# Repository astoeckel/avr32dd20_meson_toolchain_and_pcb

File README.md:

# AVR32DD20 Meson Toolchain and Breadboard Adapter PCB

**[Meson](https://mesonbuild.com/)-based toolchain for the [Microchip AVR32DD20 µC](https://www.microchip.com/en-us/product/AVR32DD20
) along with a simple breadboard adapter PCB.**

> **Note**  
> While I hope that this repository may turn out useful, please be aware that it was mainly created as a reference for myself.

> **Warning**  
> I'm not an electrical engineer; please use the PCB design with utmost caution.

At the time of creating this repository, information on how to use the newer AVR µCs (DA, DB, DD, series) with fully open-source toolchains was rather spotty.
This repository has hence been created to provide a simple example that demonstrates how to compile code for these new µCs (specifically, the AVR32DD20) with the meson build system.
<div align="center">

</div>

## Meson Toolchain

### Compile the test program

To compile the test program (see  [`src/main.c`](src/main.c)), follow the following steps.
1. **Install `avrdude` and the `avr-gcc` toolchain, as well as `meson` build and `ninja`.**  
   On Fedora Linux, simply run
   ```sh
   sudo dnf install avrdude avr-gcc avr-gcc-c++ avr-binutils ninja meson
   ```
1. **Clone this repository**
   ```sh
    git clone https://github.com/astoeckel/avr32dd20_meson_toolchain_and_pcb
    cd avr32dd20_meson_toolchain_and_pcb
   ```
1. **Edit the `path` constant in `avr-unknown-gcc.txt`**  
   This constant should point at your copy of the Git repository. Right now, `meson` does not support relative paths in the toolchain definition, so the absolute path has to be inserted by hand.
3. **Create a build directory and compile**  
   ```sh
   mkdir build; cd build
   meson setup --cross-file=../avr-unknown-gcc.txt ..
   ninja
   ```

### Flash the test program

To flash the test program using `avrdude` and a `jtag2udpi`-compatible programmer (I'm using a [Diamex EXA-PROG](https://www.diamex.de/dxshop/EXA-PROG-AVR-ISP-und-UPDI-STM32-NXP-ESP)), simply run
```sh
ninja flash
```
Edit [`meson.build`](meson.build) to change the programmer parameters.

## PCB

The PCB is a simple adapter for putting AVR32DD20 in the SOIC20 onto a breadboard.
All KiCAD project files are located in the [board](board/kicad) folder; you can find the final Gerber files for production with [JLCPCB](https://jlcpcb.com/) in the [gerber](board/gerber) folder.

### Features

* **UPDI programming header**  
  The PCB includes a standard 6-pin UPDI programming header. Note that no extra resistors or diodes are included; this board assumes that you have a proper UPDI programmer that includes all required circuitry.
* **Bypass capacitors**  
  There is some space on the PCB to for 10n and 100n bypass capacitors attached to the VCC and VIO lines.
* **Quarz crystal**  
  There is some space for a quartz-crystal on the back side, along with the corresponding capacitors.

# License information

### Third-party sources

This repository contains code from various thrid-parties:

* `avrdude.conf`  
  This file has been adapted from the `jtag2updi` project (see https://github.com/ElTangas/jtag2updi); the file was extended to include the `avr32dd20` part.
* `part_definition`  
  These files have been copied from the Microchip AVR-Dx Series Device Support pack. See https://packs.download.microchip.com/ for more information.
* `avr-unknown-gcc.txt`  
  This file has been adapted from Jussi Pakkanen's Meson Arduino Project: https://github.com/jpakkane/mesonarduino

Apart from these directories, and unless noted differently, the files in this repository are licensed as follows:

### Hardware schematics

    Copyright Andreas Stöckel 2022.
    
    This documentation describes Open Hardware and is licensed under the
    CERN OHL v. 1.2. You may redistribute and modify this documentation under
    the terms of the CERN OHL v.1.2. (http://ohwr.org/cernohl). This
    documentation is distributed WITHOUT ANY EXPRESS OR IMPLIED WARRANTY,
    INCLUDING OF MERCHANTABILITY, SATISFACTORY QUALITY AND FITNESS FOR A
    PARTICULAR PURPOSE. Please see the CERN OHL v.1.2 for applicable conditions.

### Software (AVR firmware and host programs)

    Copyright (c) 2022 Andreas Stöckel

    Permission is hereby granted, free of charge, to any person obtaining a copy
    of this software and associated documentation files (the "Software"), to deal
    in the Software without restriction, including without limitation the rights
    to use, copy, modify, merge, publish, distribute, sublicense, and/or sell
    copies of the Software, and to permit persons to whom the Software is
    furnished to do so, subject to the following conditions:

    The above copyright notice and this permission notice shall be included in all
    copies or substantial portions of the Software.

    THE SOFTWARE IS PROVIDED "AS IS", WITHOUT WARRANTY OF ANY KIND, EXPRESS OR
    IMPLIED, INCLUDING BUT NOT LIMITED TO THE WARRANTIES OF MERCHANTABILITY,
    FITNESS FOR A PARTICULAR PURPOSE AND NONINFRINGEMENT. IN NO EVENT SHALL THE
    AUTHORS OR COPYRIGHT HOLDERS BE LIABLE FOR ANY CLAIM, DAMAGES OR OTHER
    LIABILITY, WHETHER IN AN ACTION OF CONTRACT, TORT OR OTHERWISE, ARISING FROM,
    OUT OF OR IN CONNECTION WITH THE SOFTWARE OR THE USE OR OTHER DEALINGS IN THE
    SOFTWARE.

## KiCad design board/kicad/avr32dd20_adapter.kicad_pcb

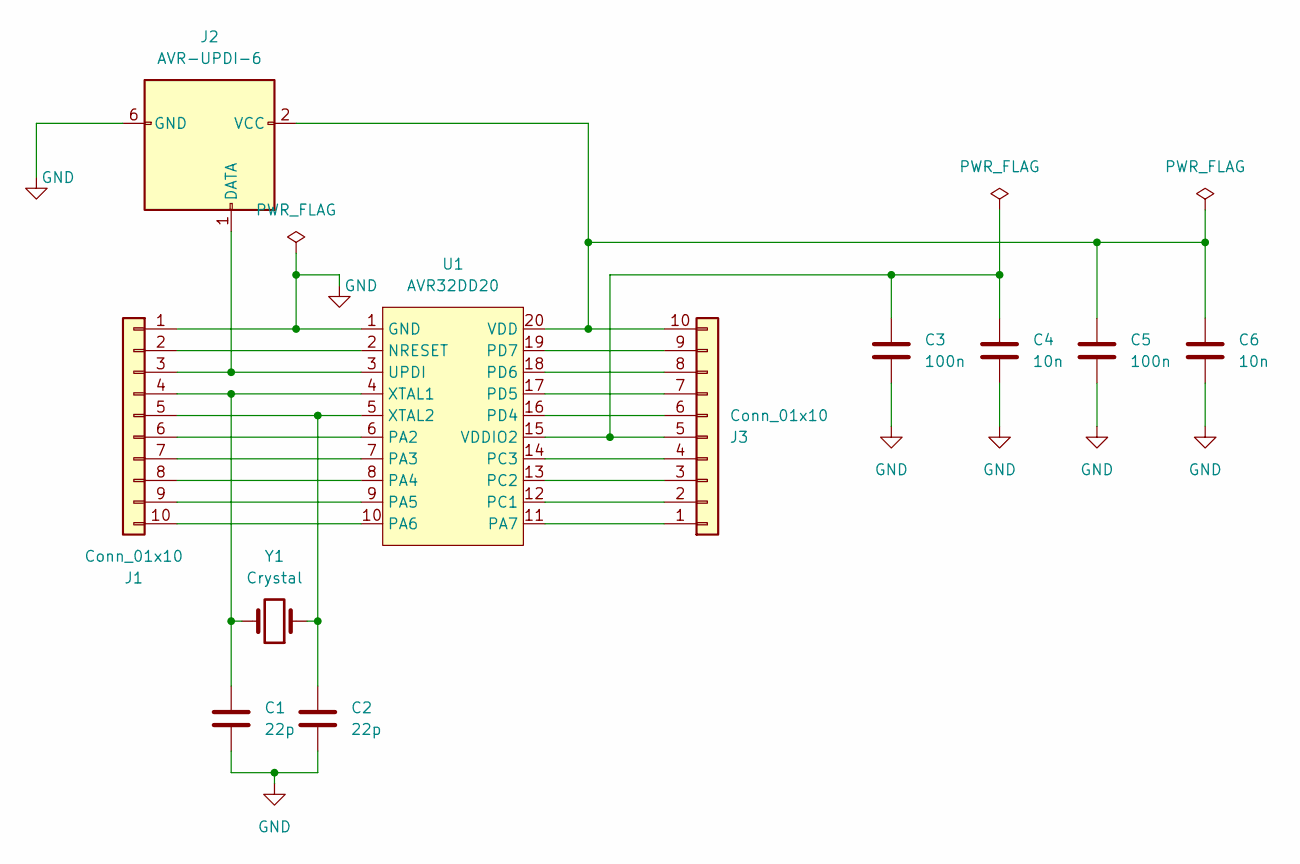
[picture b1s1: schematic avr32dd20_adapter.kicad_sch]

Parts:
C1, C2: 22p; C_0805_2012Metric_Pad1.18x1.45mm_HandSolder
C3, C5: 100n; C_1206_3216Metric_Pad1.33x1.80mm_HandSolder
C4, C6: 10n; C_1206_3216Metric_Pad1.33x1.80mm_HandSolder
J1, J3: Conn_01x10; PinHeader_1x10_P2.54mm_Vertical
J2: AVR-UPDI-6; PinHeader_2x03_P2.54mm_Vertical
U1: AVR32DD20; SOIC-20W_7.5x12.8mm_P1.27mm
Y1: Crystal; Crystal_SMD_HC49-SD_HandSoldering

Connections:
GND: C1.2, C2.2, C3.1, C4.1, C5.1, C6.1, J1.1, J2.6 (GND), U1.1 (GND)
unnamed: C1.1, J1.4, U1.4 (XTAL1), Y1.2
unnamed: C2.1, J1.5, U1.5 (XTAL2), Y1.1
unnamed: C3.2, C4.2, J3.5, U1.15 (VDDIO2)
unnamed: C5.2, C6.2, J2.2 (VCC), J3.10, U1.20 (VDD)
unnamed: J1.3, J2.1 (DATA), U1.3 (UPDI)
unnamed: J1.2, U1.2 (NRESET)
unnamed: J1.6, U1.6 (PA2)
unnamed: J1.7, U1.7 (PA3)
unnamed: J1.8, U1.8 (PA4)
unnamed: J1.9, U1.9 (PA5)
unnamed: J1.10, U1.10 (PA6)
unnamed: J3.1, U1.11 (PA7)
unnamed: J3.2, U1.12 (PC1)
unnamed: J3.3, U1.13 (PC2)
unnamed: J3.4, U1.14 (PC3)
unnamed: J3.6, U1.16 (PD4)
unnamed: J3.7, U1.17 (PD5)
unnamed: J3.8, U1.18 (PD6)
unnamed: J3.9, U1.19 (PD7)

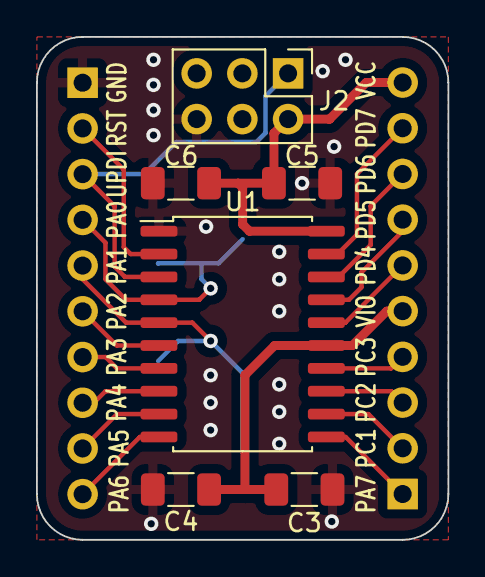
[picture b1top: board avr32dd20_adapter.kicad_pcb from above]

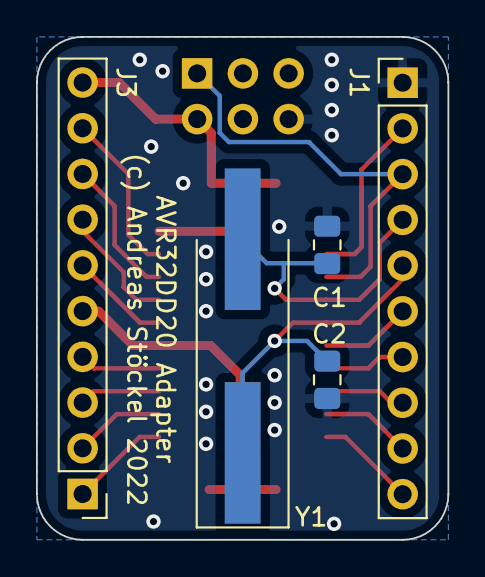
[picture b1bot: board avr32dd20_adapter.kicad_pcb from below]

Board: 2 copper layers, 22.9 x 27.9 mm, 11 parts (5 on the bottom side), 20 nets.

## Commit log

2022-11-11 Add header image
2022-11-12 Change license
2022-11-20 Also flash the `rodata` section onto the AVR
